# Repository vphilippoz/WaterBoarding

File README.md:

# WaterBoarding

This project is under developpment.

When uploaded to an ESP32, this code allows any user to toggle a water pump from a web interface. The ESP32 hosts a web page such that any device on the same network can interract with it.

## Requirements

### Arduino IDE

1. Install the esp32 board support by Espressif Systems
1. Select Tools > USB CDC On Boot > Enabled from the Arduino IDE menus (required to make Serial.print work on ESP32 boards)

## Software structure

The software is split in modules.

### Backend

This module controls the pumps using GPIOs and displays the pump state on the LED.

Public functions:
- _setup_: Required to setup the pins of the board prior to any other operation.
- _toggle_pump_: Change the state of a given pump
- _set_pump_: Activate a given pump
- _reset_pump_: Deactivate a given pump
- _deliver_ml_: Activate a given pump until the desired water quantity is delivered

Private functions:
- _set_LED_: Set the LED color according to the pumps states. Is called automatically by _set_pump_ and _reset_pump_ functions.

### Web interface

This module serves an HTML page to let a user interract with the watering system. 

N.B.: Currently, the HTML page is stored as a hardcoded string of text. For developpement, it is easier to work on _/data/index.html_ and copy paste the entire file content in the string when finished.

Public functions:
- _setup_: It defines the routes by linking the HTTP requests to backend functions. Also, it handles connection to wifi.

Private functions:
- _handle_root_: Sends the HTML page content to the client at connection.
- _handle_toggle_: When the client clicks on a "Démarrer la pompe X" button, this handler is called. It calls a backend function to toggle the corresponding pump.
- _handle_deliver_: When the client clicks on "Arroser" button, this handler is called. It extracts the pump ID and the amount to deliver from the request. Then, it calls a backend function to deliver the correct amount of liquid on the corresponding pump.
- _handle_cancel_: When the client clicks on "Annuler" button, this handler is called. It extracts the pump ID from the request. Then, it calls a backend function to stop the corresponding pump.

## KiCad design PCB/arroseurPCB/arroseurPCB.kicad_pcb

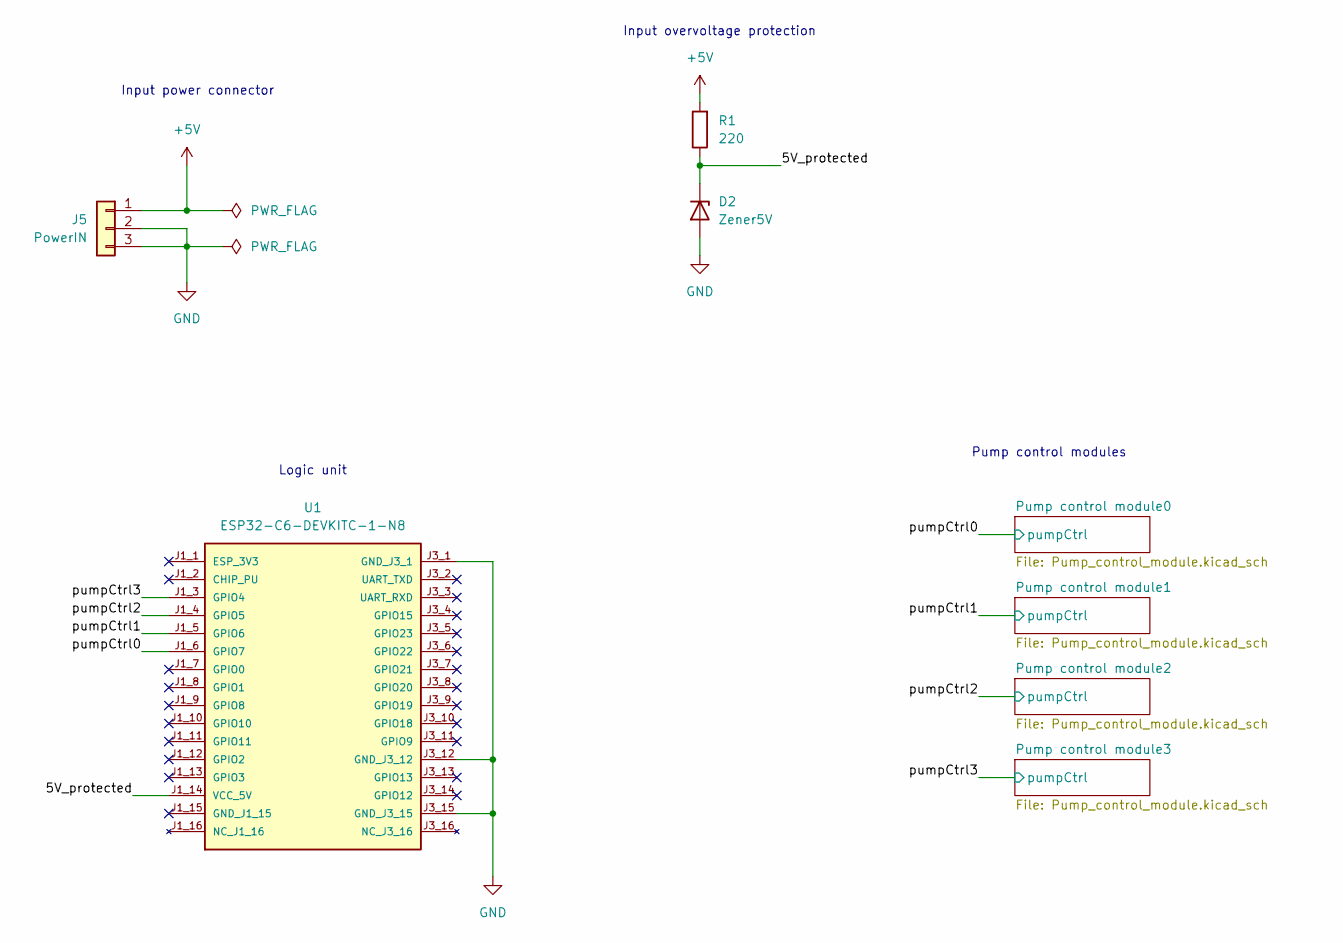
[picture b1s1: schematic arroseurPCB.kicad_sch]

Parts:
D2: Zener5V; D_DO-41_SOD81_P7.62mm_Horizontal
J5: PowerIN; PJ-112AH
R1: 220; R_Axial_DIN0309_L9.0mm_D3.2mm_P15.24mm_Horizontal
U1: ESP32-C6-DEVKITC-1-N8; MODULE_ESP32-C6-DEVKITC-1-N8; PARTREV 1.3

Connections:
+5V: J5.1, R1.2; also elsewhere on the board
/5V_protected: D2.1 (K), R1.1, U1.J1_14 (VCC_5V)
/pumpCtrl0: U1.J1_6 (GPIO7); also elsewhere on the board
/pumpCtrl1: U1.J1_5 (GPIO6); also elsewhere on the board
/pumpCtrl2: U1.J1_4 (GPIO5); also elsewhere on the board
/pumpCtrl3: U1.J1_3 (GPIO4); also elsewhere on the board
GND: D2.2 (A), J5.2, J5.3, U1.J3_1 (GND_J3_1), U1.J3_12 (GND_J3_12), U1.J3_15 (GND_J3_15); also elsewhere on the board

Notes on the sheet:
Logic unit
Input power connector
Input overvoltage protection
Pump control modules

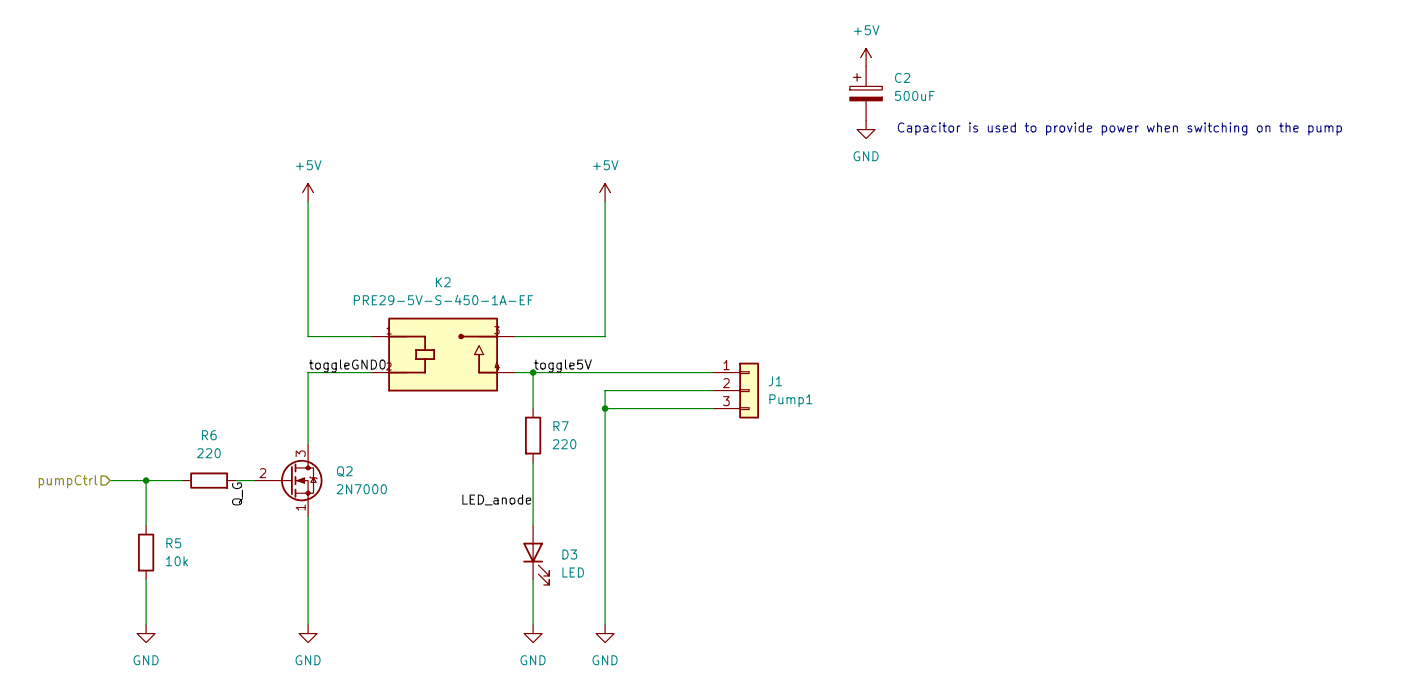
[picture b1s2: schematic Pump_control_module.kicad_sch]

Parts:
C2: 500uF; CP_Radial_D6.3mm_P2.50mm
D3: LED; LED_D5.0mm
J1: Pump1; PJ-112AH
K2: PRE29-5V-S-450-1A-EF; RELAY_PRE29-5V-S-450-1A-EF
Q2: 2N7000; TO-92L_HandSolder
R5: 10k; R_Axial_DIN0309_L9.0mm_D3.2mm_P15.24mm_Horizontal
R6, R7: 220; R_Axial_DIN0309_L9.0mm_D3.2mm_P15.24mm_Horizontal

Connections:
+5V: C2.1, K2.1, K2.3; also elsewhere on the board
/Pump control module0/LED_anode: D3.2 (A), R7.2
/Pump control module0/Q_G: Q2.2 (G), R6.2
/Pump control module0/toggle5V: J1.1, K2.4, R7.1
/Pump control module0/toggleGND0: K2.2, Q2.3 (D)
/pumpCtrl0: R5.1, R6.1; also elsewhere on the board
GND: C2.2, D3.1 (K), J1.2, J1.3, Q2.1 (S), R5.2; also elsewhere on the board

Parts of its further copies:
C1, C3, C4: 500uF; CP_Radial_D6.3mm_P2.50mm
D1, D4, D5: LED; LED_D5.0mm
J2: Pump1; PJ-112AH
K1, K3, K4: PRE29-5V-S-450-1A-EF; RELAY_PRE29-5V-S-450-1A-EF
Q1, Q3, Q4: 2N7000; TO-92L_HandSolder
R2, R8, R11: 10k; R_Axial_DIN0309_L9.0mm_D3.2mm_P15.24mm_Horizontal
R3, R4, R9, R10, R12, R13: 220; R_Axial_DIN0309_L9.0mm_D3.2mm_P15.24mm_Horizontal

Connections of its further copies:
+5V: C1.1, C3.1, C4.1, K1.1, K1.3, K3.1, K3.3, K4.1, K4.3; also elsewhere on the board
/Pump control module1/LED_anode: D1.2 (A), R4.2
/Pump control module1/Q_G: Q1.2 (G), R3.2
/Pump control module1/toggle5V: J2.1, K1.4, R4.1
/Pump control module1/toggleGND0: K1.2, Q1.3 (D)
/Pump control module2/LED_anode: D4.2 (A), R10.2
/Pump control module2/Q_G: Q3.2 (G), R9.2
/Pump control module2/toggle5V: K3.4, R10.1; also elsewhere on the board
/Pump control module2/toggleGND0: K3.2, Q3.3 (D)
/Pump control module3/LED_anode: D5.2 (A), R13.2
/Pump control module3/Q_G: Q4.2 (G), R12.2
/Pump control module3/toggle5V: K4.4, R13.1; also elsewhere on the board
/Pump control module3/toggleGND0: K4.2, Q4.3 (D)
/pumpCtrl1: R2.1, R3.1; also elsewhere on the board
/pumpCtrl2: R8.1, R9.1; also elsewhere on the board
/pumpCtrl3: R11.1, R12.1; also elsewhere on the board
GND: C1.2, C3.2, C4.2, D1.1 (K), D4.1 (K), D5.1 (K), J2.2, J2.3, Q1.1 (S), Q3.1 (S), Q4.1 (S), R2.2, R8.2, R11.2; also elsewhere on the board

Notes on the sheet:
Capacitor is used to provide power when switching on the pump

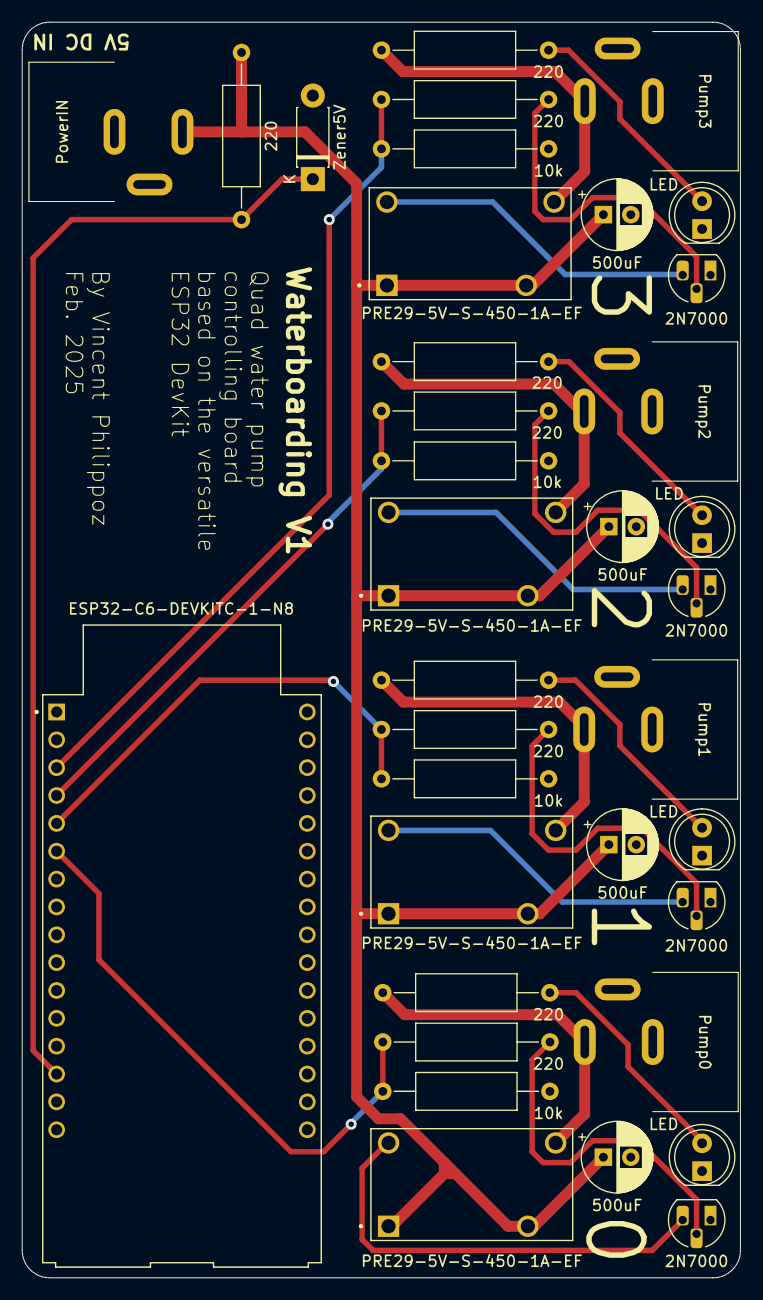
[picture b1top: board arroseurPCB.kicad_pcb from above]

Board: 2 copper layers, 65.5 x 114.5 mm, 36 parts (0 on the bottom side), 23 nets.

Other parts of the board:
J3: Pump2; PJ-112AH
J4: Pump3; PJ-112AH

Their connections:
/Pump control module2/toggle5V: J3.1; also elsewhere on the board
/Pump control module3/toggle5V: J4.1; also elsewhere on the board
GND: J3.2, J3.3, J4.2, J4.3; also elsewhere on the board

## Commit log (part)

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2025-03-24 Minimal example (untested)
2025-03-24 Added readme
2025-03-24 Include PCB and 3D files
2025-03-24 Minimalist version working
2025-03-25 Created working backend module (without LED)
2025-03-26 Added web interface module
2025-03-26 Added docstrings
2025-03-27 Working web interface with external callback
2025-03-27 Adapted main to modular architecture
2025-03-27 Tiny mod: added nbPumps as parameter for web setup
2025-03-28 Working LED indicator (only last toggled visible)
2025-03-28 LED unique color for any pump state
2025-03-31 Set and reset pump func added
2025-04-02 WORKS ON PCB ! (+ VERBOSE flag codewide)
2025-04-04 4 centered buttons
2025-04-04 Variable color & text on button for state feedback
2025-04-04 Added title to web page
2025-04-07 Tiny mistake in html
2025-04-07 Pump index corection
2025-04-07 Working backend, uncalibrated. No UI yet.
2025-04-25 Unfinished
2025-10-10 UI & frontend should work, to test.
2025-10-10 Doc added (and updated a docstring)
2025-10-13 Create scheduler (not tested)
2025-10-15 deliver_ml not working (inspect where)
2025-10-17 Fixed front-backend communication issue with simpler requests
2025-10-17 Adapted handle_toggle to have consistent request format across application
2025-10-17 WIP timezone setting
